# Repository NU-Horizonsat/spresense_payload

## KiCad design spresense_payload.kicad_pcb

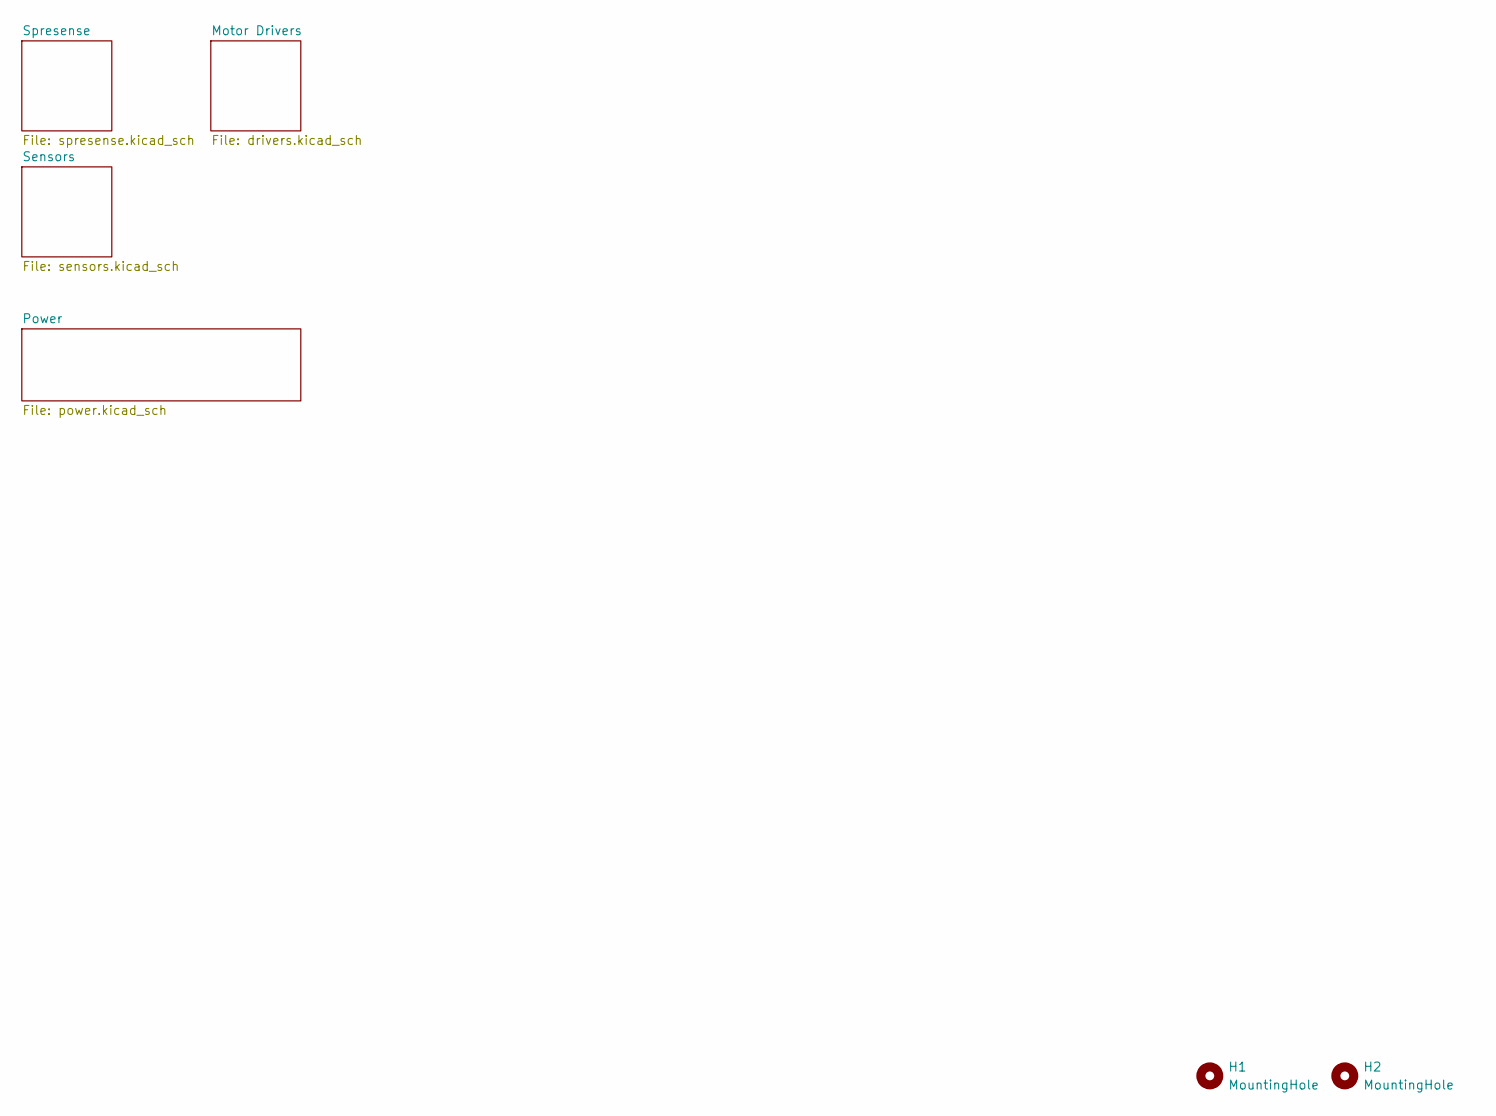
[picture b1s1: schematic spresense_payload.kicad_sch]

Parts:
H1, H2: MountingHole

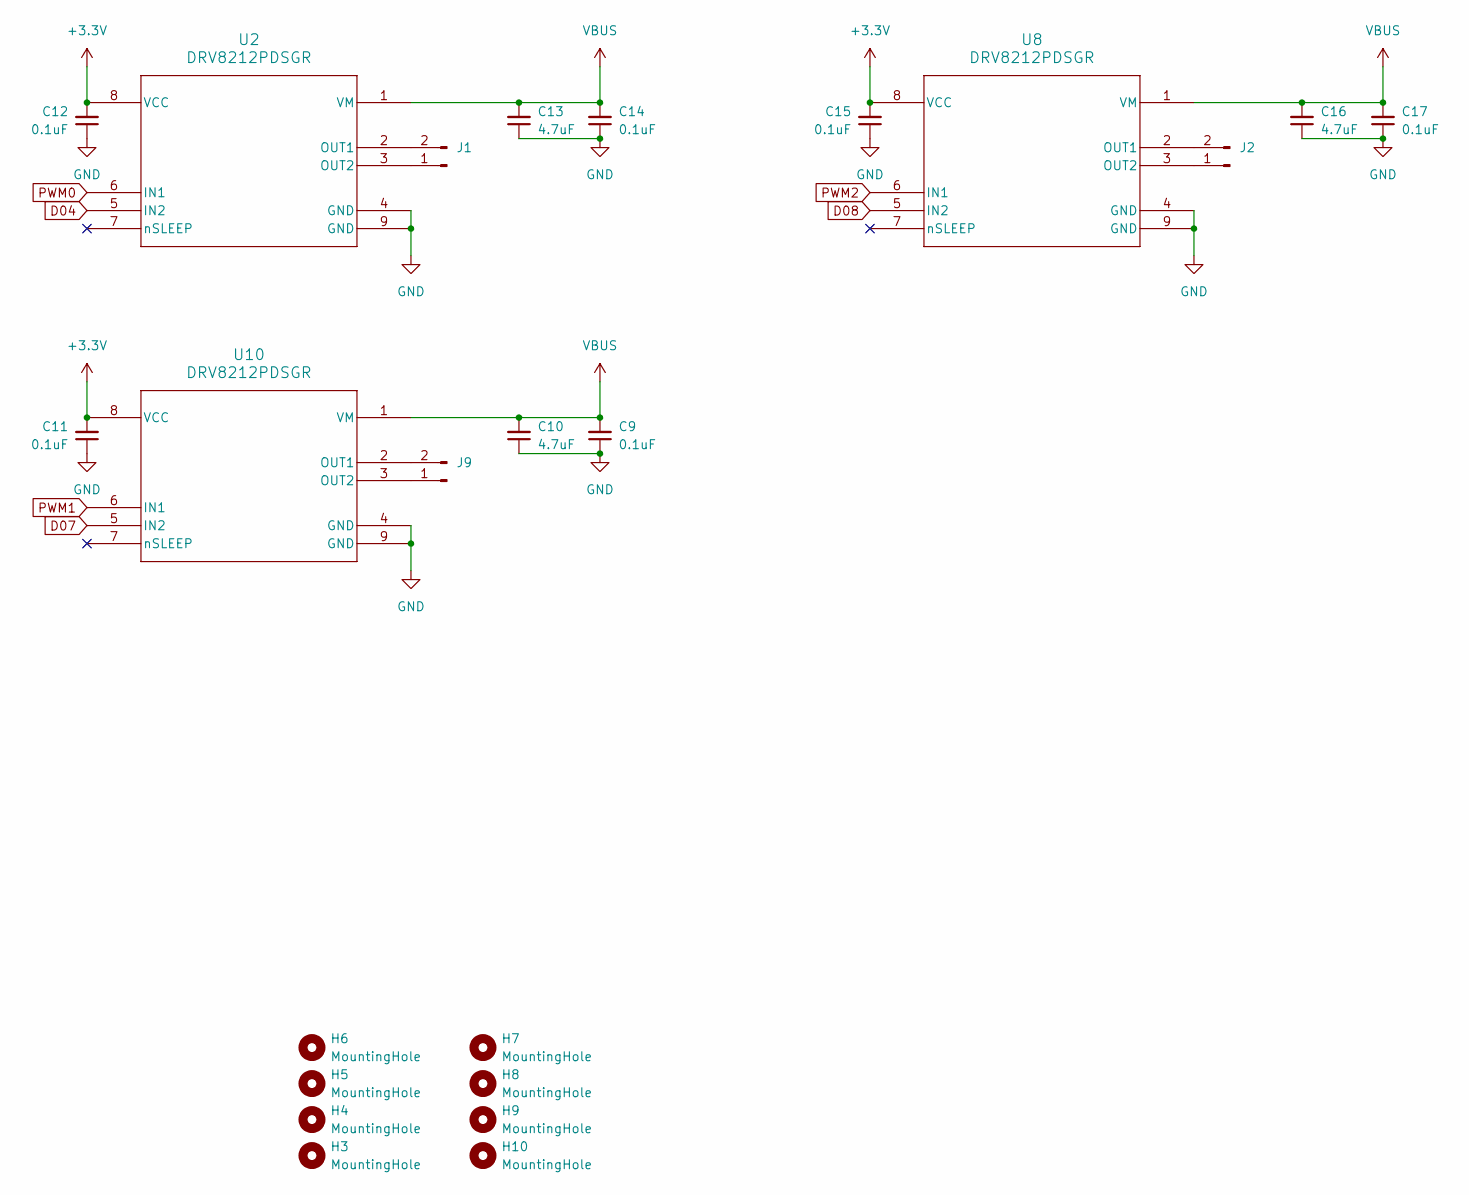
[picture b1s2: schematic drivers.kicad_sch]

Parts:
C9, C11, C12, C14, C15, C17: 0.1uF; C_0402_1005Metric
C10, C13, C16: 4.7uF; C_0402_1005Metric
H3, H4, H5, H6, H7, H8, H9, H10: MountingHole; MountingHole_2.2mm_M2
J1, J2, J9: Conn_01x02_Pin; JST_SH_BM02B-SRSS-TB_1x02-1MP_P1.00mm_Vertical
U2, U8, U10: DRV8212PDSGR; WSON8_DSG_TEX

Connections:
+3.3V: C11.2, C12.2, C15.2, U2.8 (VCC), U8.8 (VCC), U10.8 (VCC); also elsewhere on the board
D04: U2.5 (IN2); also elsewhere on the board
D07: U10.5 (IN2); also elsewhere on the board
D08: U8.5 (IN2); also elsewhere on the board
GND: C9.1, C10.1, C11.1, C12.1, C13.1, C14.1, C15.1, C16.1, C17.1, U2.4 (GND), U2.9 (GND), U8.4 (GND), U8.9 (GND), U10.4 (GND), U10.9 (GND); also elsewhere on the board
unnamed: J1.1, U2.3 (OUT2)
unnamed: J1.2, U2.2 (OUT1)
unnamed: J2.1, U8.3 (OUT2)
unnamed: J2.2, U8.2 (OUT1)
unnamed: J9.1, U10.3 (OUT2)
unnamed: J9.2, U10.2 (OUT1)
PAYLOAD_BATT: C9.2, C10.2, C13.2, C14.2, C16.2, C17.2, U2.1 (VM), U8.1 (VM), U10.1 (VM); also elsewhere on the board
PWM0: U2.6 (IN1); also elsewhere on the board
PWM1: U10.6 (IN1); also elsewhere on the board
PWM2: U8.6 (IN1); also elsewhere on the board

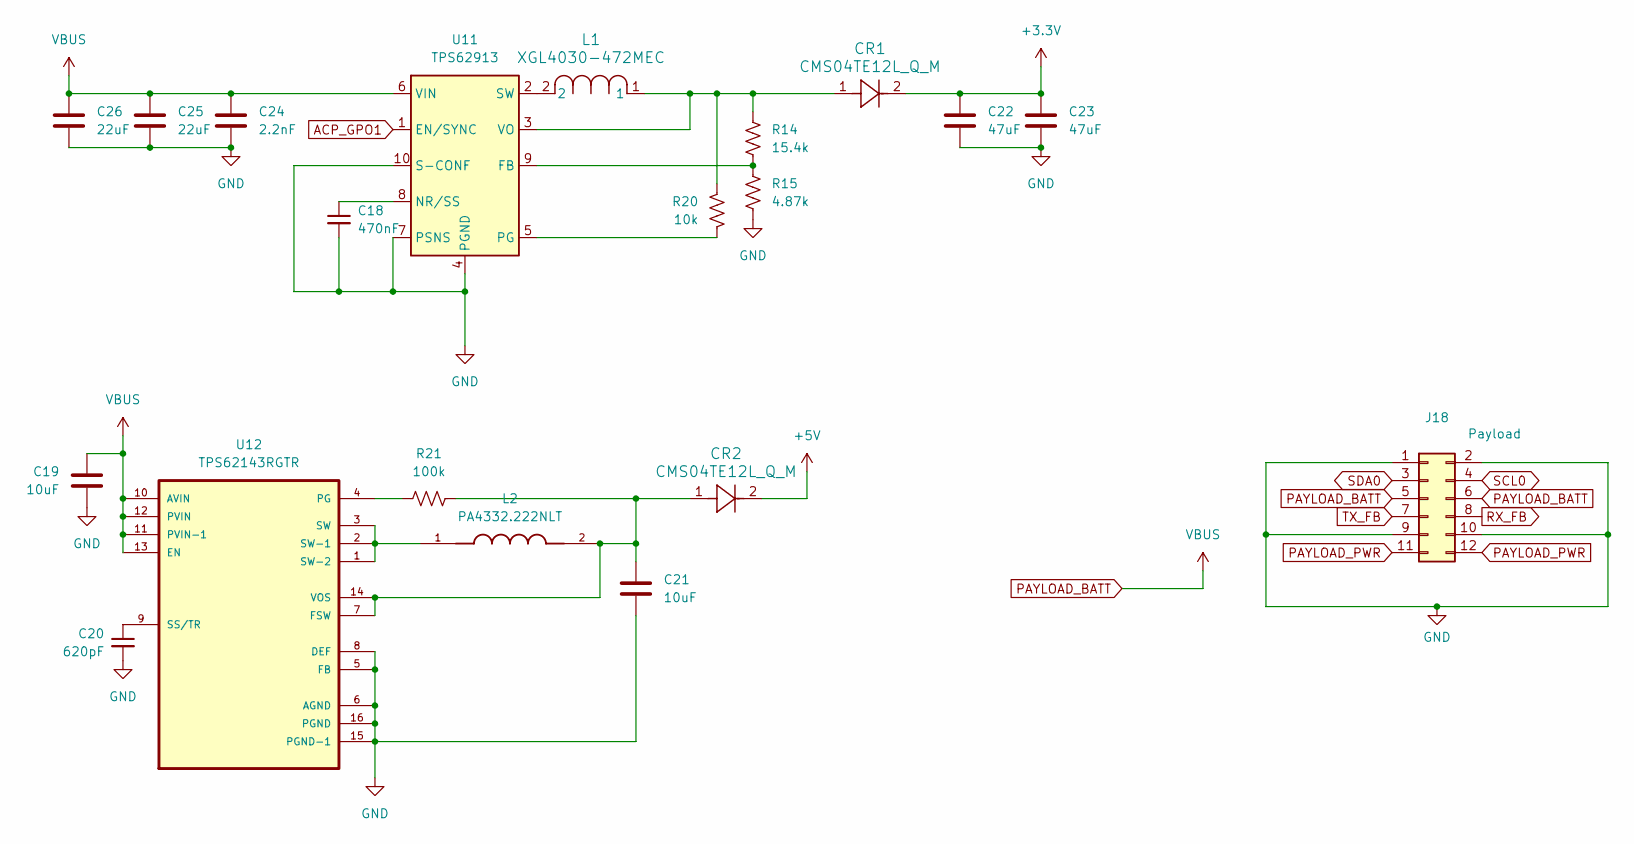
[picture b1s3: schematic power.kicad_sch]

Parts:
C18: 470nF; C_0402_1005Metric
C19, C21: 10uF; C_0603_1608Metric
C20: 620pF; C_0402_1005Metric
C22, C23: 47uF; C_0603_1608Metric
C24: 2.2nF; C_0603_1608Metric
C25, C26: 22uF; C_0603_1608Metric
CR1, CR2: CMS04TE12L_Q_M; M-FLAT_TOS
J18: Payload; Hirose_DF11-12DP-2DSA_2x06_P2.00mm_Vertical
L1: XGL4030-472MEC; IND_XGL4030_COC
L2: PA4332.222NLT; IND_PA4332.222NLT; PARTREV 12/23
R14: 15.4k; R_0402_1005Metric
R15: 4.87k; R_0402_1005Metric
R20: 10k; R_0402_1005Metric
R21: 100k; R_0402_1005Metric
U11: TPS62913; Texas_RPU0010A_VQFN-HR-10_2x2mm_P0.5mm
U12: TPS62143RGTR; QFN50P300X300X100-17N

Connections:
+3.3V: C22.1, C23.1, CR1.2; also elsewhere on the board
+5V: CR2.2; also elsewhere on the board
ACP_GPO1: U11.1 (EN/SYNC); also elsewhere on the board
GND: C18.2, C19.2, C20.2, C21.2, C22.2, C23.2, C24.2, C25.2, C26.2, J18.1, J18.2, J18.9, J18.10, R15.2, U11.4 (PGND), U11.7 (PSNS), U11.10 (S-CONF), U12.5 (FB), U12.6 (AGND), U12.8 (DEF), U12.15 (PGND-1), U12.16 (PGND); also elsewhere on the board
unnamed: R14.2, R15.1, U11.9 (FB)
unnamed: C18.1, U11.8 (NR/SS)
unnamed: R20.2, U11.5 (PG)
unnamed: L1.2, U11.2 (SW)
unnamed: CR1.1, L1.1, R14.1, R20.1, U11.3 (VO)
unnamed: C21.1, CR2.1, L2.2, R21.2, U12.7 (FSW), U12.14 (VOS)
unnamed: R21.1, U12.4 (PG)
unnamed: C20.1, U12.9 (SS/TR)
unnamed: L2.1, U12.1 (SW-2), U12.2 (SW-1), U12.3 (SW)
PAYLOAD_BATT: C19.1, C24.1, C25.1, C26.1, J18.5, J18.6, U11.6 (VIN), U12.10 (AVIN), U12.11 (PVIN-1), U12.12 (PVIN), U12.13 (EN); also elsewhere on the board
PAYLOAD_PWR: J18.11, J18.12
RX_FB: J18.8; also elsewhere on the board
SCL0: J18.4
SDA0: J18.3
TX_FB: J18.7; also elsewhere on the board

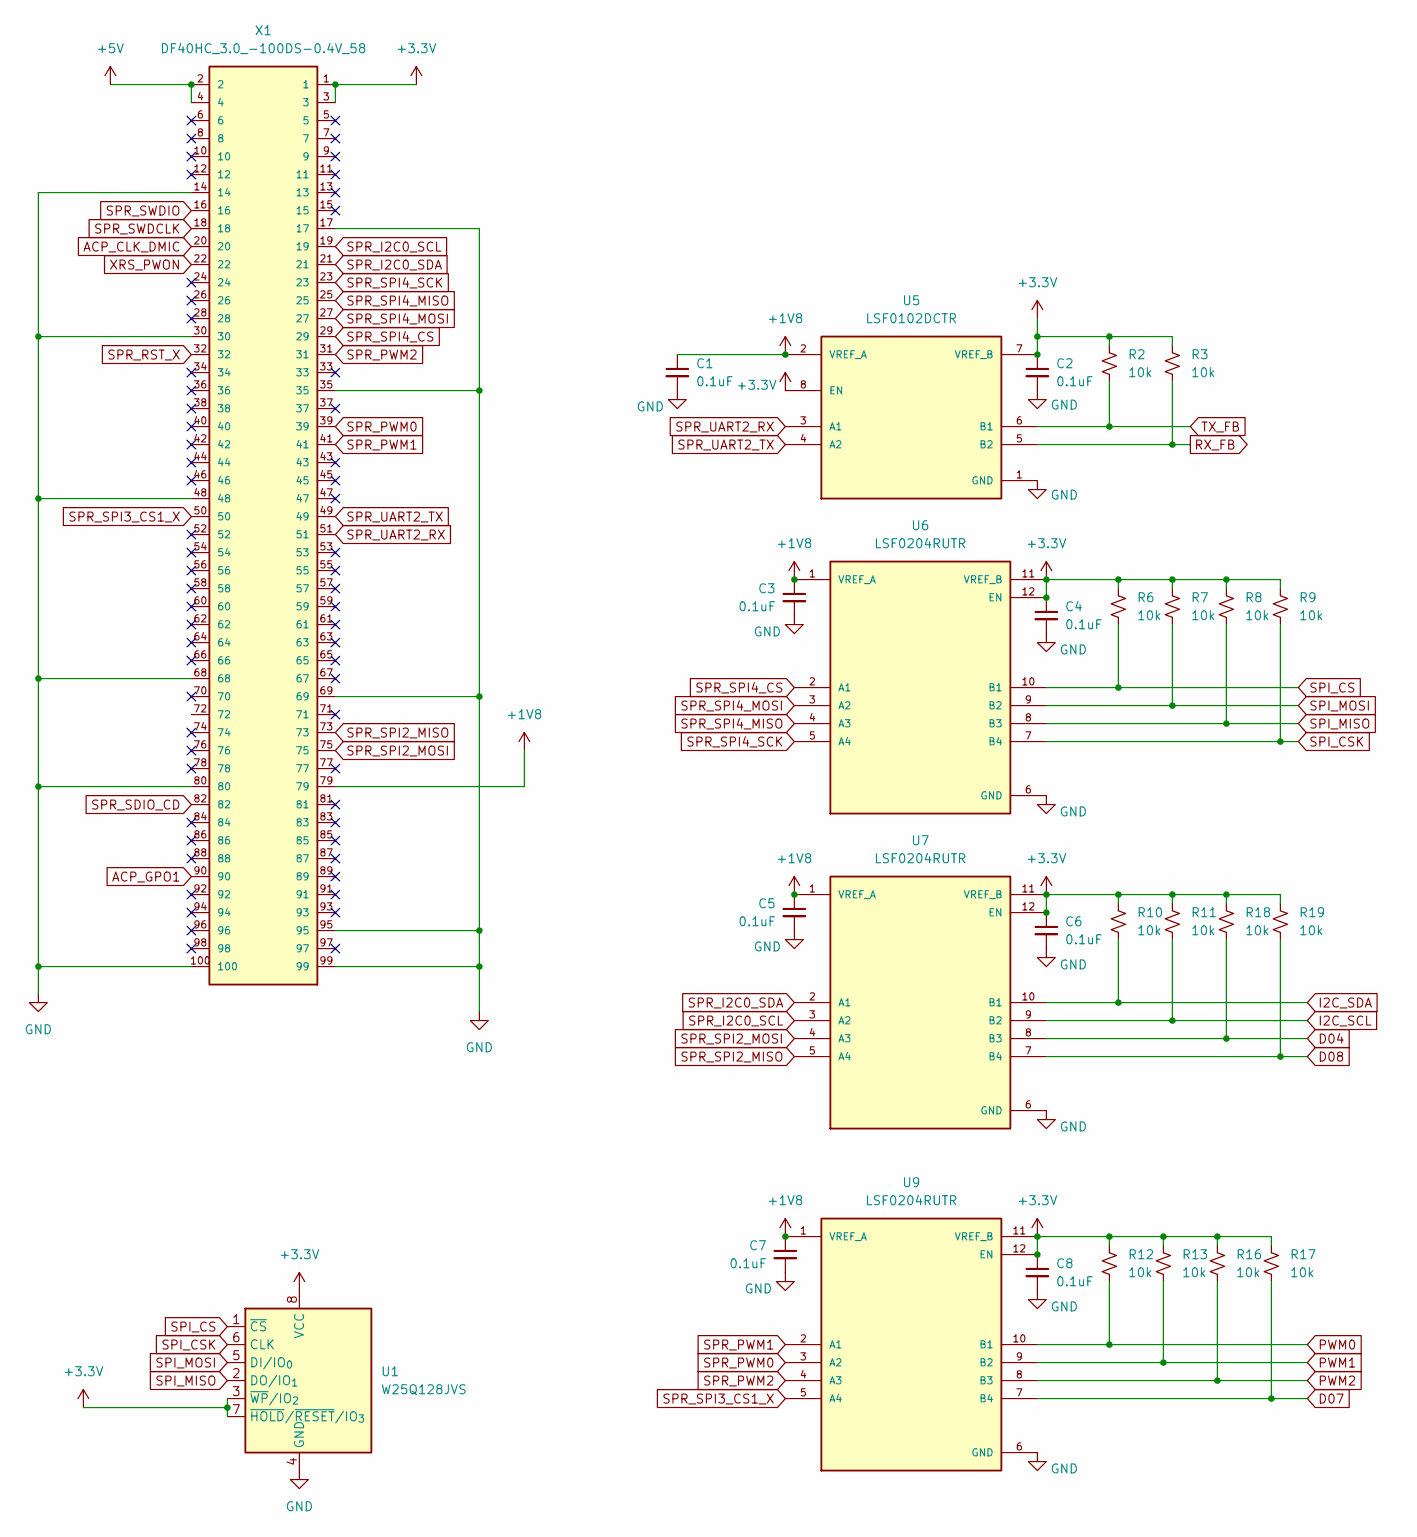
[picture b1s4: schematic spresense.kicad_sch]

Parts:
C1, C2, C3, C4, C5, C6, C7, C8: 0.1uF; C_0402_1005Metric
R2, R3, R6, R7, R8, R9, R10, R11, R12, R13, R16, R17, R18, R19: 10k; R_0402_1005Metric
U1: W25Q128JVS; SOIC-8_5.3x5.3mm_P1.27mm
U5: LSF0102DCTR; SOP65P400X130-8N; PARTREV J
U6, U7, U9: LSF0204RUTR; IC_LSF0204RUTR; PARTREV 4210580/C 06/12
X1: DF40HC_3.0_-100DS-0.4V_58; HRS_DF40HC_3.0_-100DS-0.4V_58

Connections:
+1V8: C1.1, C3.1, C5.1, C7.1, U5.2 (VREF_A), U6.1 (VREF_A), U7.1 (VREF_A), U9.1 (VREF_A), X1.79
+3.3V: C2.1, C4.1, C6.1, C8.1, R2.1, R3.1, R6.1, R7.1, R8.1, R9.1, R10.1, R11.1, R12.1, R13.1, R16.1, R17.1, R18.1, R19.1, U1.3 (~WP/IO_{2}), U1.7 (~HOLD/~RESET/IO_{3}), U1.8 (VCC), U5.7 (VREF_B), U5.8 (EN), U6.11 (VREF_B), U6.12 (EN), U7.11 (VREF_B), U7.12 (EN), U9.11 (VREF_B), U9.12 (EN), X1.1, X1.3; also elsewhere on the board
+5V: X1.2, X1.4; also elsewhere on the board
ACP_CLK_DMIC: X1.20
ACP_GPO1: X1.90; also elsewhere on the board
D04: R18.2, U7.8 (B3); also elsewhere on the board
D07: R17.2, U9.7 (B4); also elsewhere on the board
D08: R19.2, U7.7 (B4); also elsewhere on the board
GND: C1.2, C2.2, C3.2, C4.2, C5.2, C6.2, C7.2, C8.2, U1.4 (GND), U5.1 (GND), U6.6 (GND), U7.6 (GND), U9.6 (GND), X1.14, X1.17, X1.30, X1.35, X1.48, X1.68, X1.69, X1.80, X1.95, X1.99, X1.100; also elsewhere on the board
I2C_SCL: R11.2, U7.9 (B2); also elsewhere on the board
I2C_SDA: R10.2, U7.10 (B1); also elsewhere on the board
PWM0: R12.2, U9.10 (B1); also elsewhere on the board
PWM1: R13.2, U9.9 (B2); also elsewhere on the board
PWM2: R16.2, U9.8 (B3); also elsewhere on the board
RX_FB: R3.2, U5.5 (B2); also elsewhere on the board
SPI_CS: R6.2, U1.1 (~CS), U6.10 (B1)
SPI_CSK: R9.2, U1.6 (CLK), U6.7 (B4)
SPI_MISO: R8.2, U1.2 (DO/IO_{1}), U6.8 (B3)
SPI_MOSI: R7.2, U1.5 (DI/IO_{0}), U6.9 (B2)
SPR_I2C0_SCL: U7.3 (A2), X1.19
SPR_I2C0_SDA: U7.2 (A1), X1.21
SPR_PWM0: U9.3 (A2), X1.39
SPR_PWM1: U9.2 (A1), X1.41
SPR_PWM2: U9.4 (A3), X1.31
SPR_RST_X: X1.32
SPR_SDIO_CD: X1.82
SPR_SPI2_MISO: U7.5 (A4), X1.73
SPR_SPI2_MOSI: U7.4 (A3), X1.75
SPR_SPI3_CS1_X: U9.5 (A4), X1.50
SPR_SPI4_CS: U6.2 (A1), X1.29
SPR_SPI4_MISO: U6.4 (A3), X1.25
SPR_SPI4_MOSI: U6.3 (A2), X1.27
SPR_SPI4_SCK: U6.5 (A4), X1.23
SPR_SWDCLK: X1.18
SPR_SWDIO: X1.16
SPR_UART2_RX: U5.3 (A1), X1.51
SPR_UART2_TX: U5.4 (A2), X1.49
TX_FB: R2.2, U5.6 (B1); also elsewhere on the board
XRS_PWON: X1.22

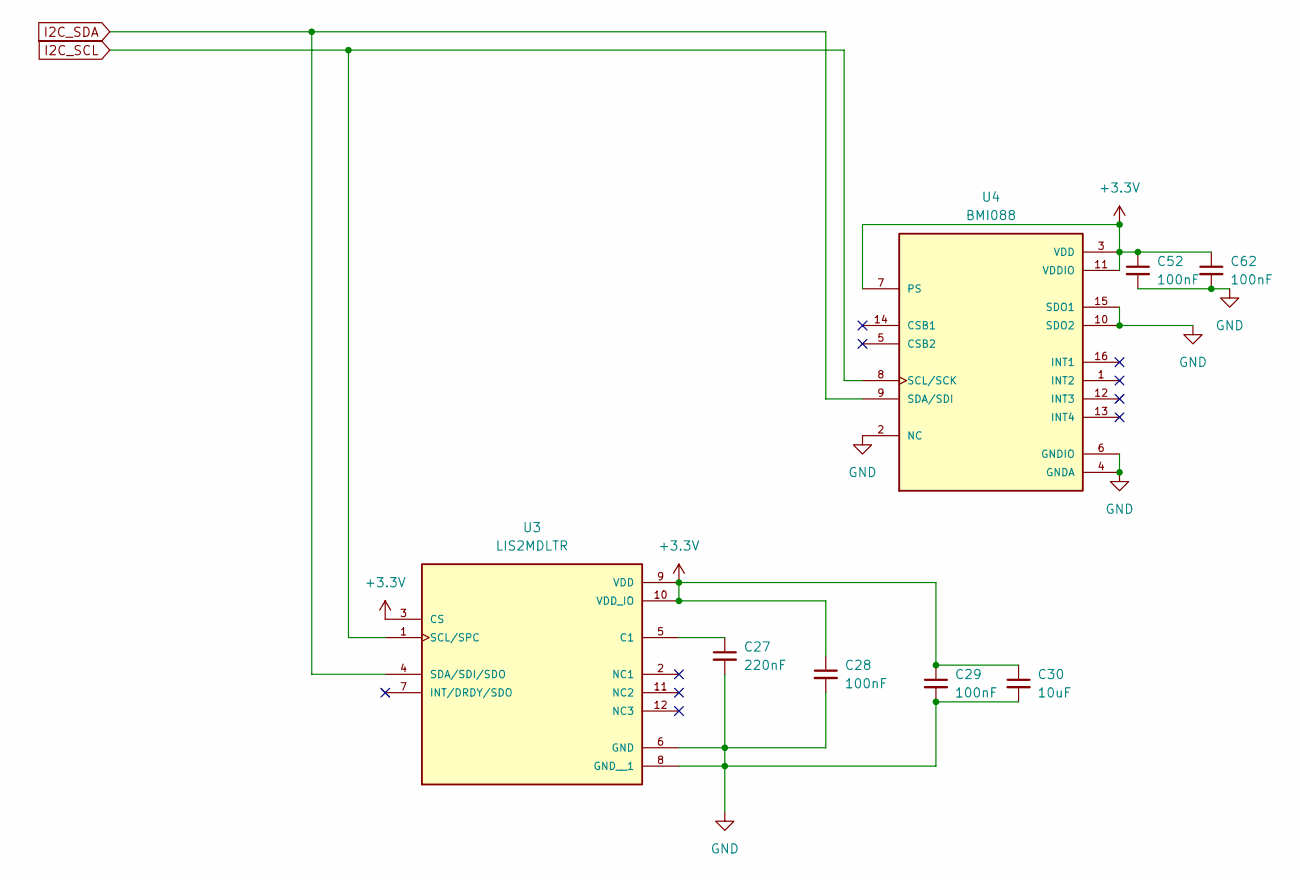
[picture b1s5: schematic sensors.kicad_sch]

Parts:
C27: 220nF; C_0402_1005Metric
C28, C29, C52, C62: 100nF; C_0402_1005Metric
C30: 10uF; C_0402_1005Metric
U3: LIS2MDLTR; PQFN50P200X200X70-12N; PARTREV Rev 5
U4: BMI088; QFN_BMI085_BOS

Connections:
+3.3V: C28.1, C29.1, C30.1, C52.1, C62.1, U3.3 (CS), U3.9 (VDD), U3.10 (VDD_IO), U4.3 (VDD), U4.7 (PS), U4.11 (VDDIO); also elsewhere on the board
GND: C27.2, C28.2, C29.2, C30.2, C52.2, C62.2, U3.6 (GND), U3.8 (GND__1), U4.2 (NC), U4.4 (GNDA), U4.6 (GNDIO), U4.10 (SDO2), U4.15 (SDO1); also elsewhere on the board
I2C_SCL: U3.1 (SCL/SPC), U4.8 (SCL/SCK); also elsewhere on the board
I2C_SDA: U3.4 (SDA/SDI/SDO), U4.9 (SDA/SDI); also elsewhere on the board
unnamed: C27.1, U3.5 (C1)

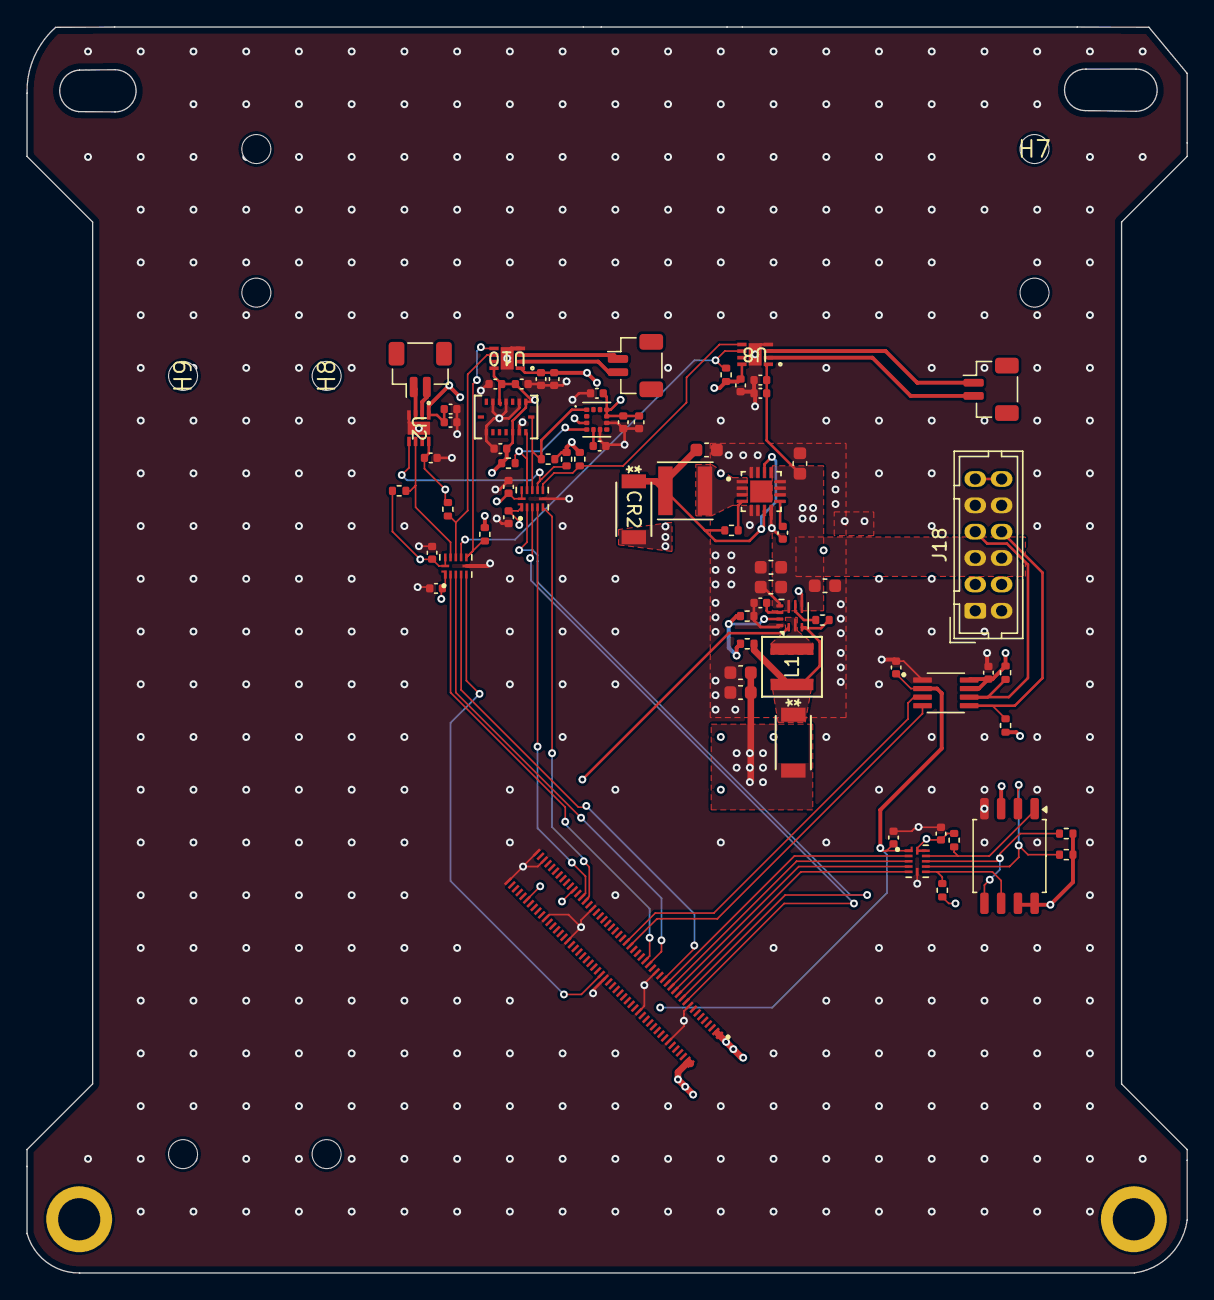
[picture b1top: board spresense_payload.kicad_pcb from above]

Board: 4 copper layers, 88.0 x 94.5 mm, 81 parts (0 on the bottom side), 51 nets.

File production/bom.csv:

Designator,Footprint,Quantity,Value,LCSC Part #
"C1, C11, C12, C14, C15, C17, C2, C3, C4, C5, C6, C7, C8, C9",0402,14,0.1uF,
"C10, C13, C16",0402,3,4.7uF,
C18,0402,1,470nF,
"C19, C21",0603,2,10uF,
C20,0402,1,620pF,
"C22, C23",0603,2,47uF,
C24,0603,1,2.2nF,
"C25, C26",0603,2,22uF,
C27,0402,1,220nF,
"C28, C29, C52, C62",0402,4,100nF,
C30,0402,1,10uF,
"CR1, CR2",M-FLAT_TOS,2,CMS04TE12L_Q_M,
"H10, H3, H4, H5, H6, H7, H8, H9",MountingHole_2.2mm_M2,8,MountingHole,
"J1, J2, J9",JST_SH_BM02B-SRSS-TB_1x02-1MP_P1.00mm_Vertical,3,Conn_01x02_Pin,
J18,Hirose_DF11-12DP-2DSA_2x06_P2.00mm_Vertical,1,Payload,
L1,IND_XGL4030_COC,1,XGL4030-472MEC,
L2,IND_PA4332.222NLT,1,PA4332.222NLT,
"R10, R11, R12, R13, R16, R17, R18, R19, R2, R20, R3, R6, R7, R8, R9",0402,15,10k,
R14,0402,1,15.4k,
R15,0402,1,4.87k,
R21,0402,1,100k,
U1,SOIC-8_5.3x5.3mm_P1.27mm,1,W25Q128JVS,
"U10, U2, U8",WSON8_DSG_TEX,3,DRV8212PDSGR,
U11,Texas_RPU0010A_VQFN-HR-10_2x2mm_P0.5mm,1,TPS62913,
U12,QFN50P300X300X100-17N,1,TPS62143RGTR,
U3,PQFN50P200X200X70-12N,1,LIS2MDLTR,
U4,QFN_BMI085_BOS,1,BMI088,
U5,SOP65P400X130-8N,1,LSF0102DCTR,
"U6, U7, U9",IC_LSF0204RUTR,3,LSF0204RUTR,
X1,HRS_DF40HC_3.0_-100DS-0.4V_58,1,DF40HC_3.0_-100DS-0.4V_58,

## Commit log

2025-08-20 Version v1 complete
2025-10-07 changed mounting holes
